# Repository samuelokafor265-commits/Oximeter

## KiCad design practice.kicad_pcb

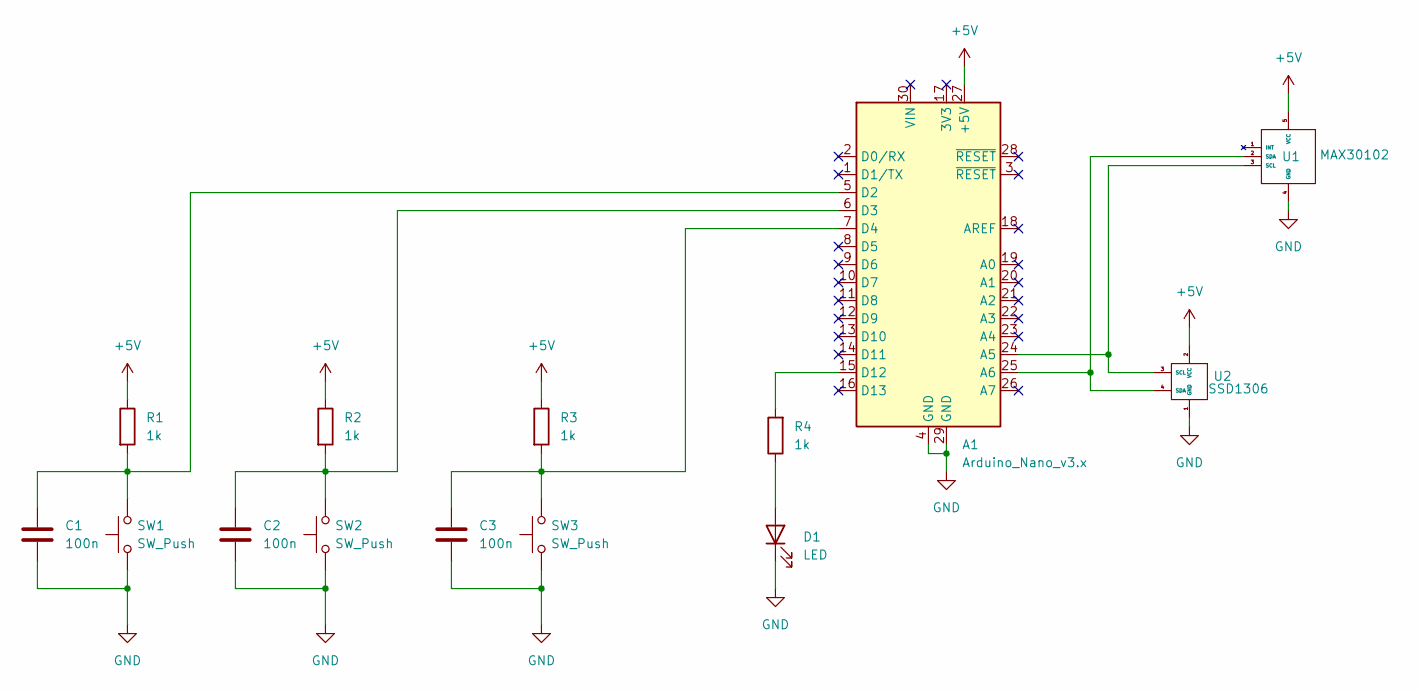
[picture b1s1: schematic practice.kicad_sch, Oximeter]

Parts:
A1: Arduino_Nano_v3.x; Arduino_Nano
C1, C2, C3: 100n; C_Disc_D4.7mm_W2.5mm_P5.00mm
D1: LED; LED_D5.0mm
R1, R2, R3, R4: 1k; R_Axial_DIN0207_L6.3mm_D2.5mm_P7.62mm_Horizontal
SW1, SW2, SW3: SW_Push; SW_PUSH_6mm
U1: MAX30102; MAX30102_Module
U2: SSD1306

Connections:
+5V: A1.27 (+5V), R1.1, R2.1, R3.1, U1.5 (VCC), U2.2 (VCC)
GND: A1.4 (GND), A1.29 (GND), C1.2, C2.2, C3.2, D1.1 (K), SW1.1, SW2.1, SW3.1, U1.4 (GND), U2.1 (GND)
unnamed: A1.24 (A5), U1.3 (SCL), U2.3 (SCL)
unnamed: A1.25 (A6), U1.2 (SDA), U2.4 (SDA)
unnamed: A1.5 (D2), C1.1, R1.2, SW1.2
unnamed: A1.6 (D3), C2.1, R2.2, SW2.2
unnamed: A1.7 (D4), C3.1, R3.2, SW3.2
unnamed: A1.15 (D12), R4.2
unnamed: D1.2 (A), R4.1

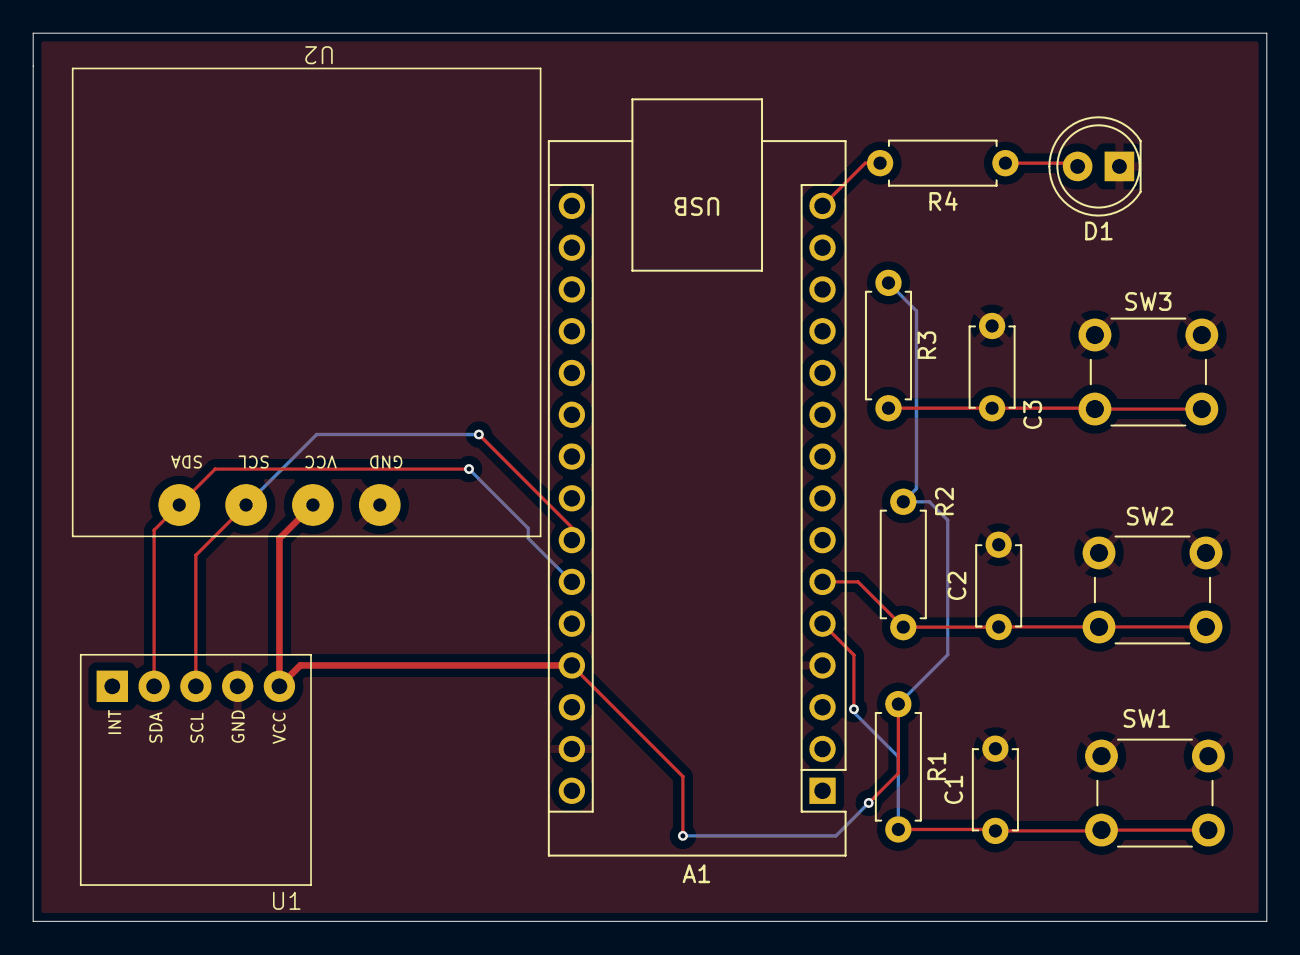
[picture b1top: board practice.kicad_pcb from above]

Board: 4 copper layers, 75.0 x 54.0 mm, 14 parts (0 on the bottom side), 9 nets.

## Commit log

2026-06-05 My First KiCAD Project
